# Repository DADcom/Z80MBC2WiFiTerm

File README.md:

Remote WiFi Terminal for Z80-MBC2
=================================

A mashup of WifiTerm for Arduino ESP 8266
and xterm.js for a Wi-Fi addon to the Z80-MBC2 
released under MIT

please see the license

 (C) Danny Arnold 2020
 Portions of this code are 
 Copyright (c) 2020 bricoleau
 Copyright (c) 2017-2019, The xterm.js authors (MIT License)
 Copyright (c) 2014-2017, SourceLair, Private Company (www.sourcelair.com) (MIT License)
 Copyright (c) 2012-2013, Christopher Jeffrey (MIT License)

Please see Releases for current release
https://github.com/DADcom/Z80MBC2WiFiTerm/releases

To-do

- Implement 'user' key support - requires updating Z80-MBC2 firmware for support
- Documentation finish documentation wiki
- ~~Kicad schematics of ESP8266 implementation~~

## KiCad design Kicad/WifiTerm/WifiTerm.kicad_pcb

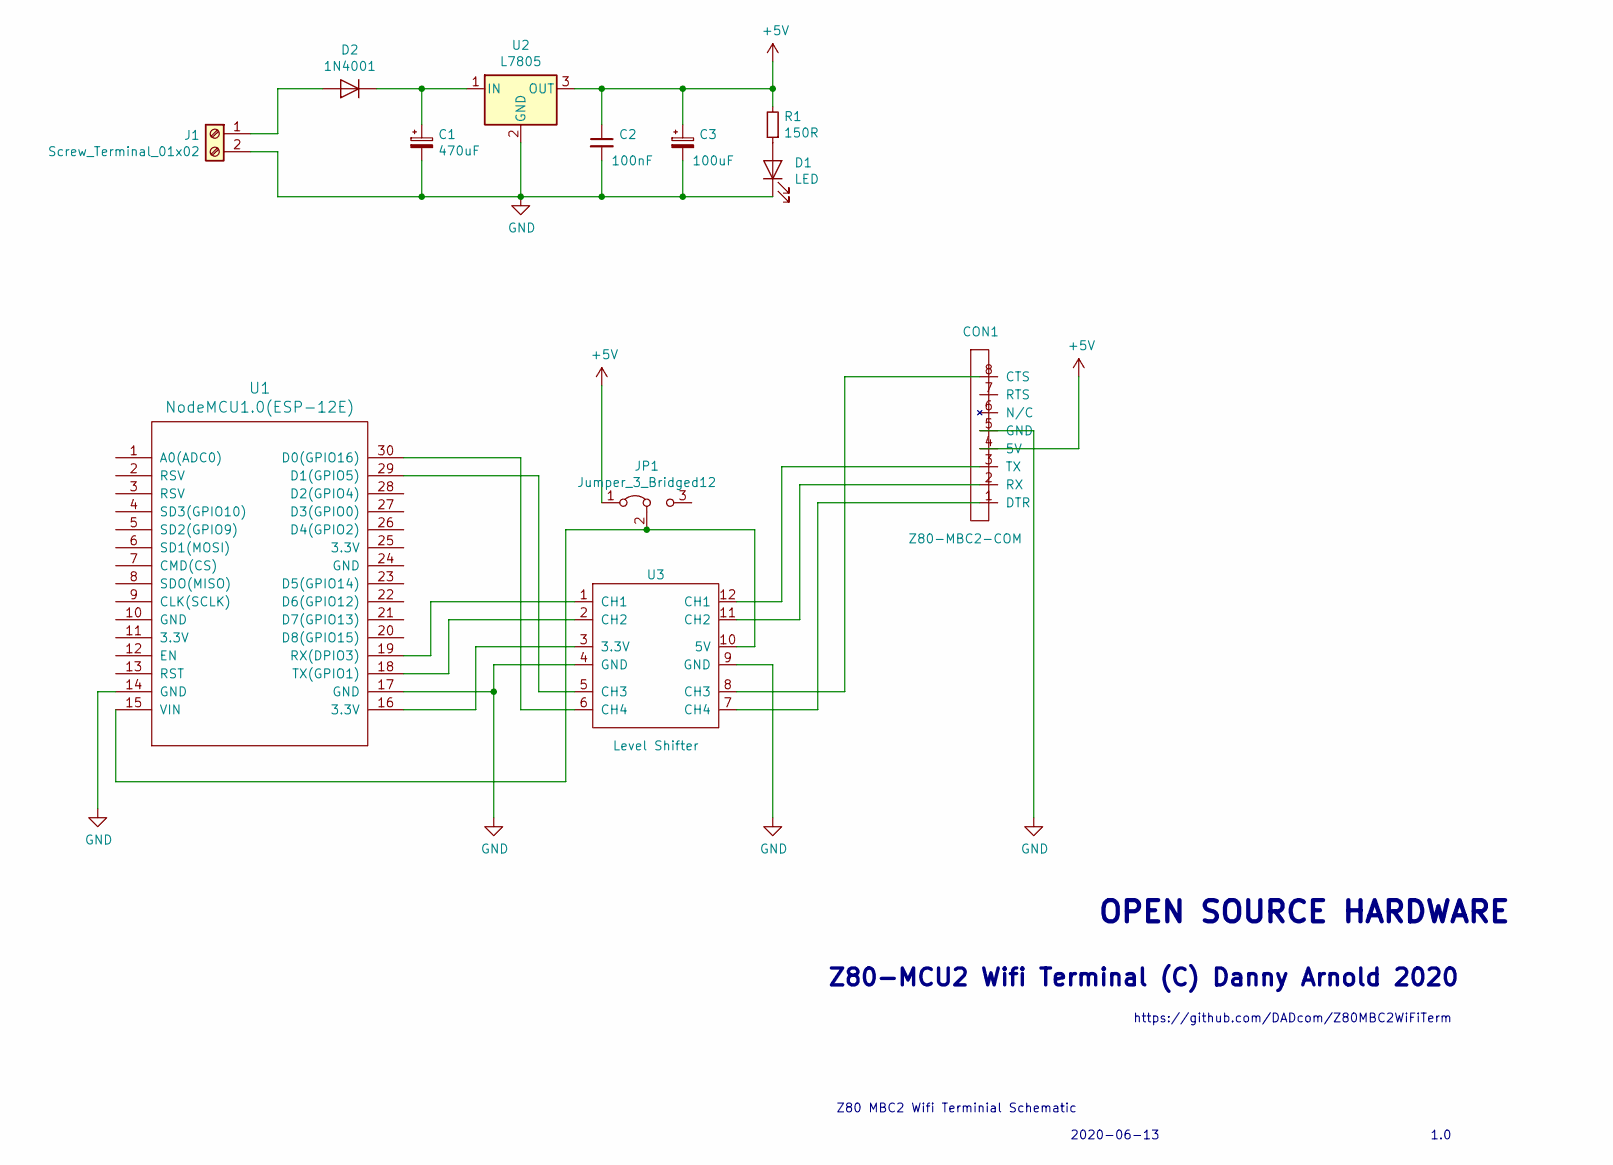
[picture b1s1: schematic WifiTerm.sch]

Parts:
C1: 470uF; CP_Radial_D14.0mm_P7.50mm
C2: 100nF; C_Rect_L7.0mm_W3.5mm_P5.00mm
C3: 100uF; CP_Radial_D6.3mm_P2.50mm
CON1: Z80-MBC2-COM; PinHeader_1x08_P2.54mm_Vertical
D1: LED; LED_D3.0mm
D2: 1N4001; D_A-405_P12.70mm_Horizontal
J1: Screw_Terminal_01x02; ScrewTerm1x02_P5.00mm
JP1: Jumper_3_Bridged12; PinHeader_1x03_P2.54mm_Vertical
R1: 150R; R_Axial_DIN0207_L6.3mm_D2.5mm_P7.62mm_Horizontal
U1: NodeMCU1.0(ESP-12E); NodeMCU1.0(12-E)
U2: L7805; TO-220-3_Vertical
U3: Level Shifter; LogicLevelShift

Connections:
+5V: C2.1, C3.1, CON1.4 (5V), JP1.1 (A), R1.2, U2.3 (OUT)
GND: C1.2, C2.2, C3.2, CON1.5 (GND), D1.1 (K), J1.2, U1.14 (GND), U1.17 (GND), U2.2 (GND), U3.4 (GND), U3.9 (GND)
unnamed: C1.1, D2.1 (K), U2.1 (IN)
unnamed: CON1.1 (DTR), U3.7 (CH4)
unnamed: CON1.2 (RX), U3.11 (CH2)
unnamed: CON1.3 (TX), U3.12 (CH1)
unnamed: CON1.8 (CTS), U3.8 (CH3)
unnamed: D1.2 (A), R1.1
unnamed: D2.2 (A), J1.1
unnamed: JP1.2 (C), U1.15 (VIN), U3.10 (5V)
unnamed: U1.16 (3.3V), U3.3 (3.3V)
unnamed: U1.18 (TX(GPIO1)), U3.2 (CH2)
unnamed: U1.19 (RX(DPIO3)), U3.1 (CH1)
unnamed: U1.29 (D1(GPIO5)), U3.5 (CH3)
unnamed: U1.30 (D0(GPIO16)), U3.6 (CH4)

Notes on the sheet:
Z80-MCU2 Wifi Terminal (C) Danny Arnold 2020
OPEN SOURCE HARDWARE
Z80 MBC2 Wifi Terminial Schematic
2020-06-13
1.0
https://github.com/DADcom/Z80MBC2WiFiTerm

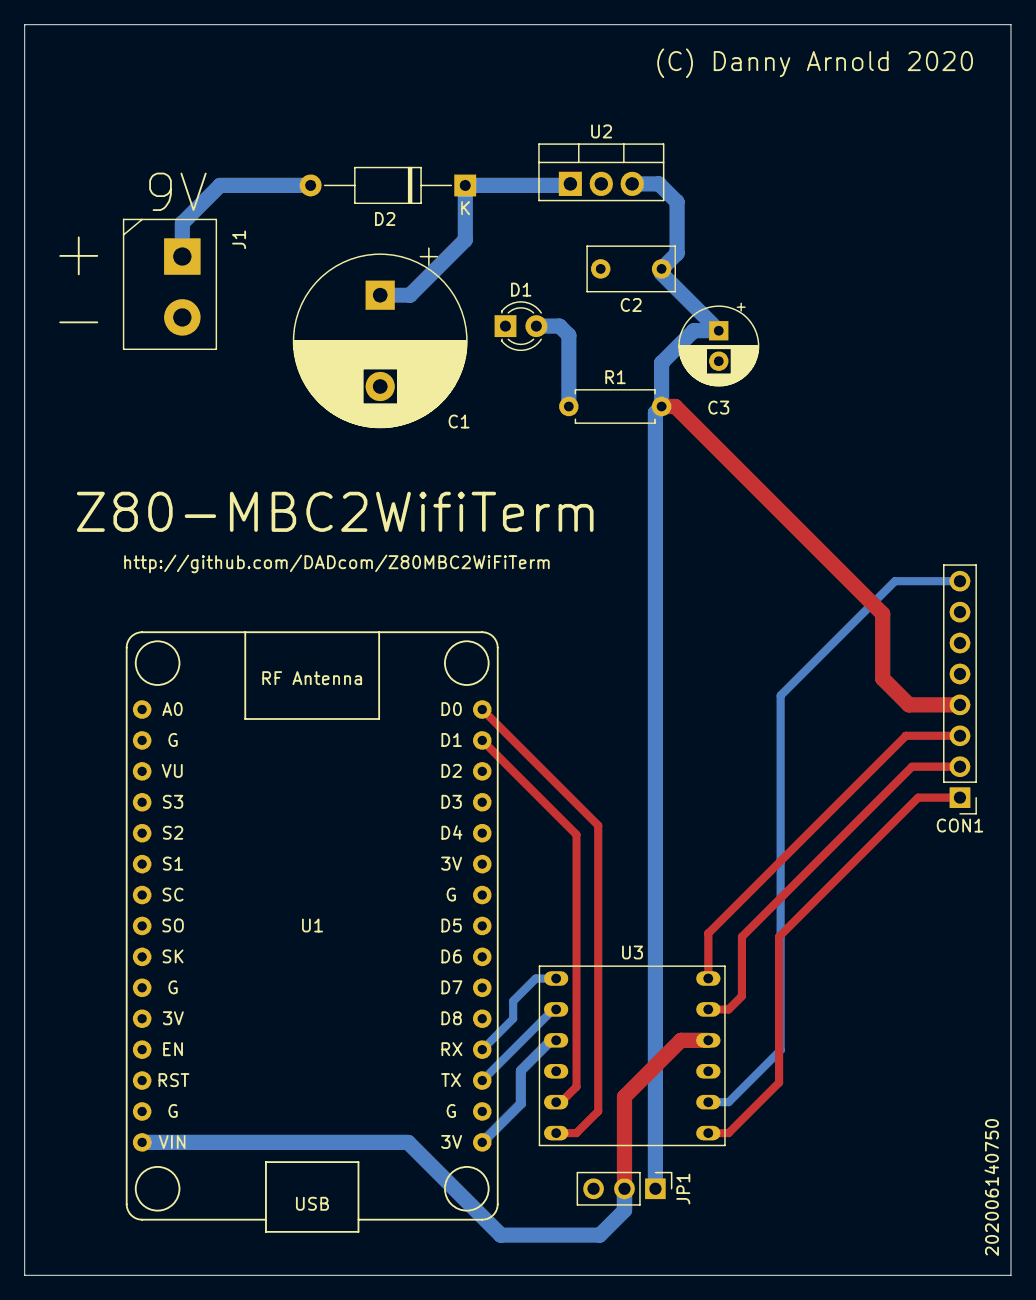
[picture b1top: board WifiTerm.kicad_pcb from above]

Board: 2 copper layers, 81.0 x 102.7 mm, 12 parts (0 on the bottom side), 15 nets.

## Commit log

2020-06-13 Update viewport
2020-06-13 Fixed mobile rendering
2020-06-13 Corrected About Github link
2020-06-13 Added Full control key support
2020-06-13 Added todo to readme
2020-06-13 Fix readme
2020-06-13 Upload images for wiki
2020-06-13 Resized image
2020-06-13 Added a gif for wiki
2020-06-13 correction to readme
2020-06-14 KiCad Update
2020-06-14 Images and update readme
2020-06-16 Added User key support
2020-06-16 Update nodemcu ino with USERkey support
2020-06-16 Created VSCode workspace
